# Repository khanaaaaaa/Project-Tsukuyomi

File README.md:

# Project-Tsukuyomi

## Zine

## What It Is & Why I Made It

A LED Chaser PCB in the form of a 'Sharingan' from the anime Naruto. I honestly did whatever and tried to do everything relatively simple and looked back at the Stasis starter project for reference. Though this was a lot different in the sheer ascpect of number of LEDs I used.

Everytime, I make a new project, I do two things: Make it some media related, and add something new everytime. I have always loved Naruto, and I was wondering how I could implement something from Naruto into a PCB, and also make it something really fun. I honestly have never worked with a lot of LEDs like this but there's a first for everything! Also the first thing I ever learned to make in hardware was a LED chaser from Stasis so roughly tried to do what I remember from there and it was very fun overall!

## How To Use It

1. Connect a 5V power source (USB or other regulated 5V supply) to the power input on the PCB.
2. Once poewr is applied, the circuit starts automatically and the LEDs begin their programmed lighting sequence.
3. The CD4017 counter and timing circuit control the LED pattern, causing the LEDs to illuminate in sequencearound the board.
4. Place the PCB on a flat surface, or display it as desired while powered.
5. If the LEDs do not light up, verify that the power supply is providing 5V and the polarity is correct.
6. If only some LEDs operate, inspect the corresponding LED, resistor, and transitor's solder joints for assembly issues.

## Schematic

## PCB

## 3D View

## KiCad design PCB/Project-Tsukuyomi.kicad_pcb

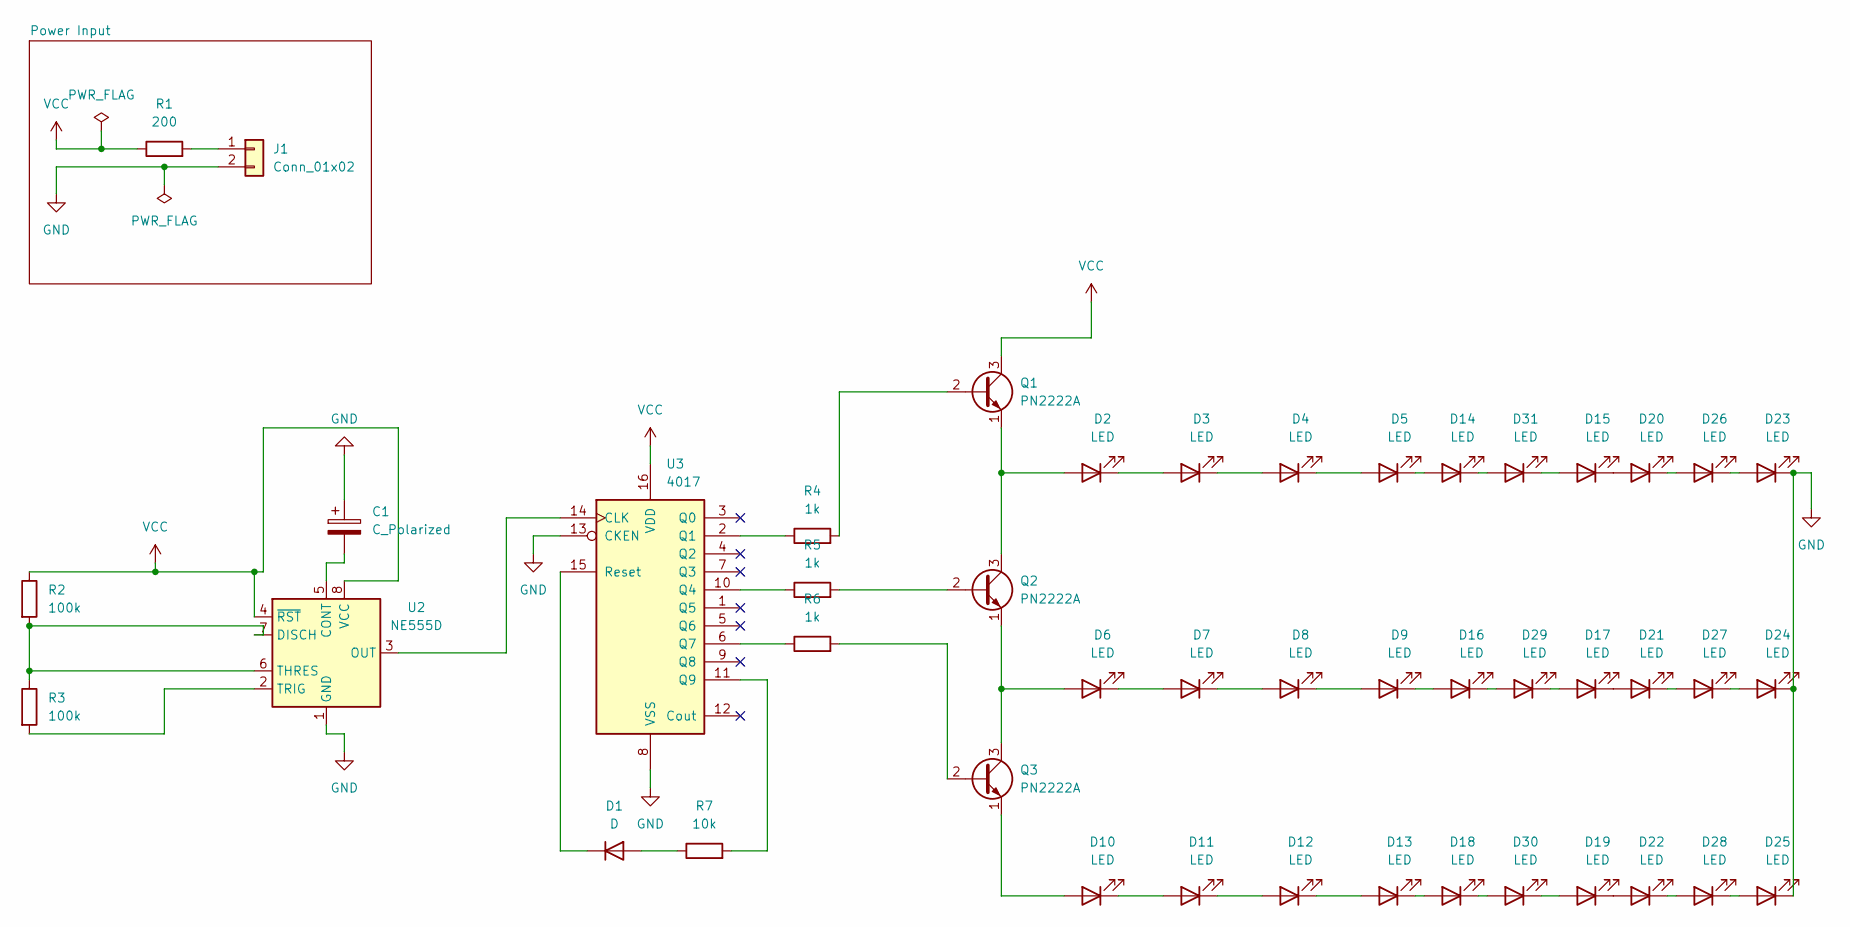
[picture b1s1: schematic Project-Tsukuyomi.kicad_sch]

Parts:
C1: C_Polarized; CP_Radial_D5.0mm_P2.50mm
D1: D; D_DO-41_SOD81_P10.16mm_Horizontal
D2, D3, D4, D5, D6, D7, D8, D9, D10, D11, D12, D13, D14, D15, D16, D17, D18, D19, D20, D21, D22, D23, D24, D25, D26, D27, D28, D29, D30, D31: LED; LED_D5.0mm
J1: Conn_01x02; PinHeader_1x02_P2.54mm_Vertical
Q1, Q2, Q3: PN2222A; TO-92_Inline
R1: 200; R_Axial_DIN0207_L6.3mm_D2.5mm_P10.16mm_Horizontal
R2, R3: 100k; R_Axial_DIN0207_L6.3mm_D2.5mm_P10.16mm_Horizontal
R4, R5, R6: 1k; R_Axial_DIN0207_L6.3mm_D2.5mm_P10.16mm_Horizontal
R7: 10k; R_Axial_DIN0207_L6.3mm_D2.5mm_P10.16mm_Horizontal
U2: NE555D; SOIC-8_3.9x4.9mm_P1.27mm
U3: 4017; DIP-16_W7.62mm

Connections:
GND: C1.1, D23.1 (K), D24.1 (K), D25.1 (K), J1.2, U2.1 (GND), U3.8 (VSS), U3.13 (CKEN)
unnamed: D1.2 (A), R7.1
unnamed: D1.1 (K), U3.15 (Reset)
unnamed: D2.2 (A), Q1.1 (E), Q2.3 (C)
unnamed: D2.1 (K), D3.2 (A)
unnamed: D3.1 (K), D4.2 (A)
unnamed: D4.1 (K), D5.2 (A)
unnamed: D6.2 (A), Q2.1 (E), Q3.3 (C)
unnamed: D6.1 (K), D7.2 (A)
unnamed: D7.1 (K), D8.2 (A)
unnamed: D8.1 (K), D9.2 (A)
unnamed: D10.2 (A), Q3.1 (E)
unnamed: D10.1 (K), D11.2 (A)
unnamed: D11.1 (K), D12.2 (A)
unnamed: D12.1 (K), D13.2 (A)
unnamed: D13.1 (K), D18.2 (A)
unnamed: D5.1 (K), D14.2 (A)
unnamed: D14.1 (K), D31.2 (A)
unnamed: D15.2 (A), D31.1 (K)
unnamed: D15.1 (K), D20.2 (A)
unnamed: D9.1 (K), D16.2 (A)
unnamed: D16.1 (K), D29.2 (A)
unnamed: D17.2 (A), D29.1 (K)
unnamed: D17.1 (K), D21.2 (A)
unnamed: D18.1 (K), D30.2 (A)
unnamed: D19.2 (A), D30.1 (K)
unnamed: D19.1 (K), D22.2 (A)
unnamed: D20.1 (K), D26.2 (A)
unnamed: D21.1 (K), D27.2 (A)
unnamed: D22.1 (K), D28.2 (A)
unnamed: D23.2 (A), D26.1 (K)
unnamed: D24.2 (A), D27.1 (K)
unnamed: D25.2 (A), D28.1 (K)
unnamed: J1.1, R1.2
unnamed: Q1.2 (B), R4.2
unnamed: Q2.2 (B), R5.2
unnamed: Q3.2 (B), R6.2
unnamed: C1.2, U2.5 (CONT)
unnamed: R2.2, R3.1, U2.6 (THRES), U2.7 (DISCH)
unnamed: U2.3 (OUT), U3.14 (CLK)
unnamed: R3.2, U2.2 (TRIG)
unnamed: R4.1, U3.2 (Q1)
unnamed: R5.1, U3.10 (Q4)
unnamed: R6.1, U3.6 (Q7)
unnamed: R7.2, U3.11 (Q9)
VCC: Q1.3 (C), R1.1, R2.1, U2.4 (~RST), U2.8 (VCC), U3.16 (VDD)

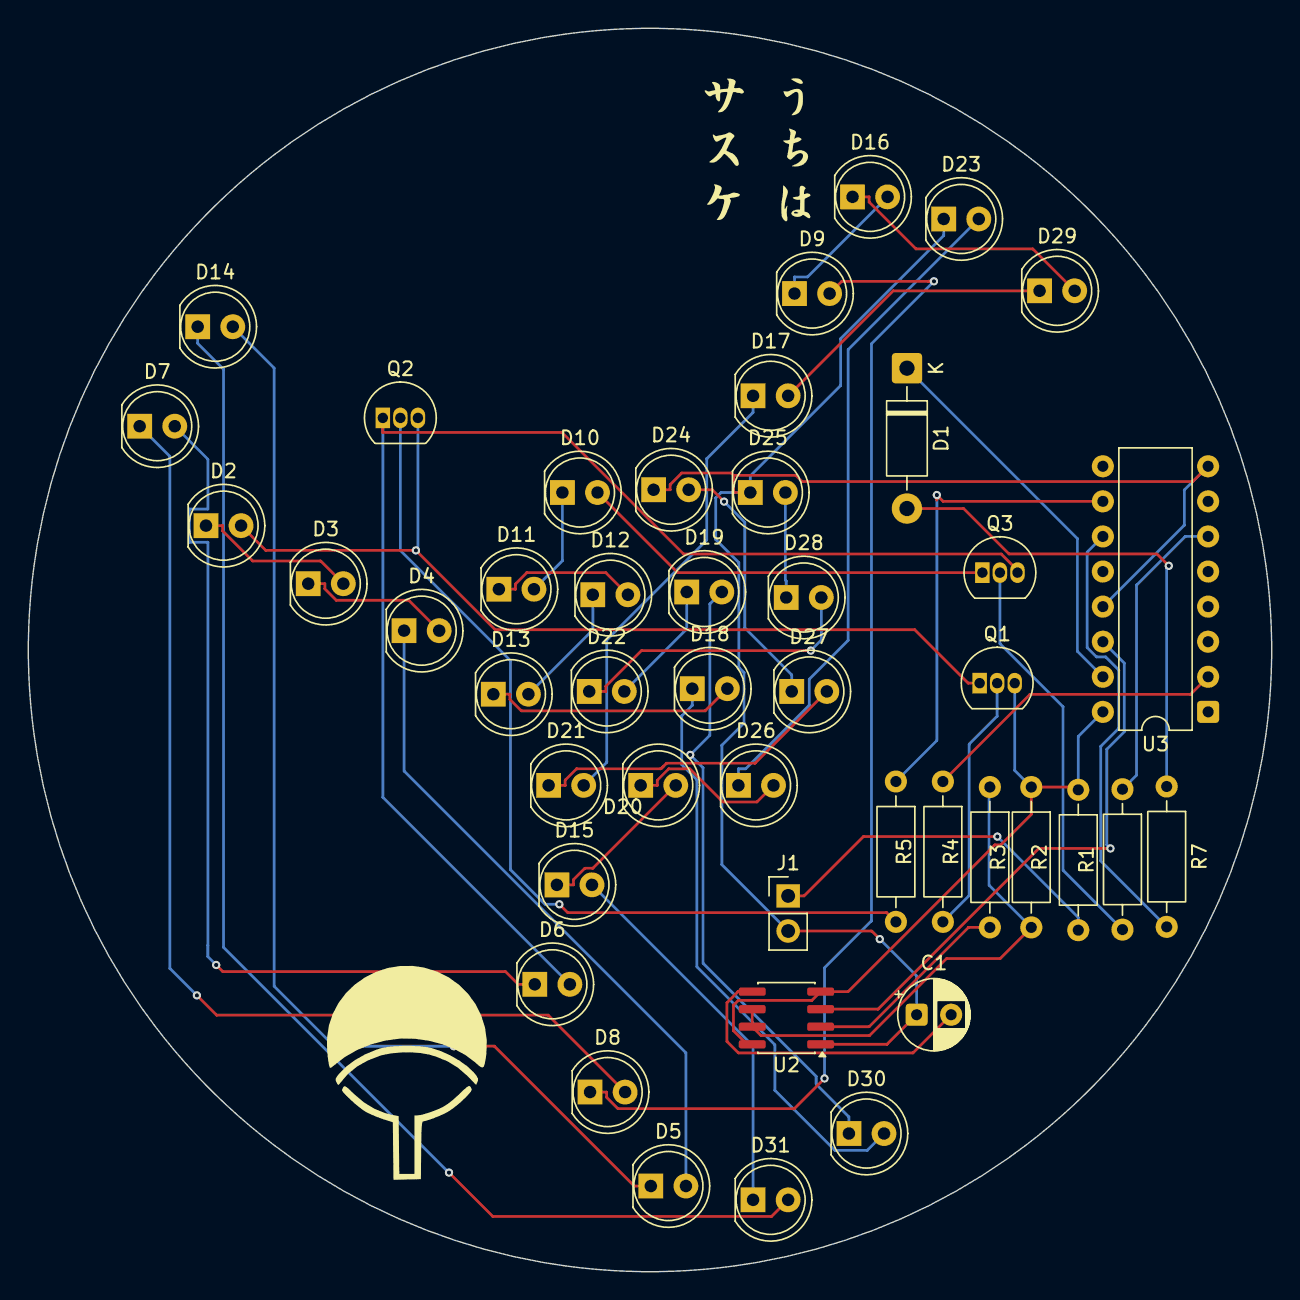
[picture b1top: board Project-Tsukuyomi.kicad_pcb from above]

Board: 2 copper layers, 90.0 x 90.0 mm, 46 parts (0 on the bottom side), 46 nets.

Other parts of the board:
‎: LOGO

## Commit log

2026-06-02 Added stuff to the README
2026-06-03 Add usage instructions to README
    Added a 'How To Use It' section with instructions for connecting and operating the LED Chaser PCB.
2026-06-03 Added the BOM and organized the files
2026-06-03 Fix typo and add JLCPCB section in README
    Corrected a typo in the description and added a section for JLCPCB.
